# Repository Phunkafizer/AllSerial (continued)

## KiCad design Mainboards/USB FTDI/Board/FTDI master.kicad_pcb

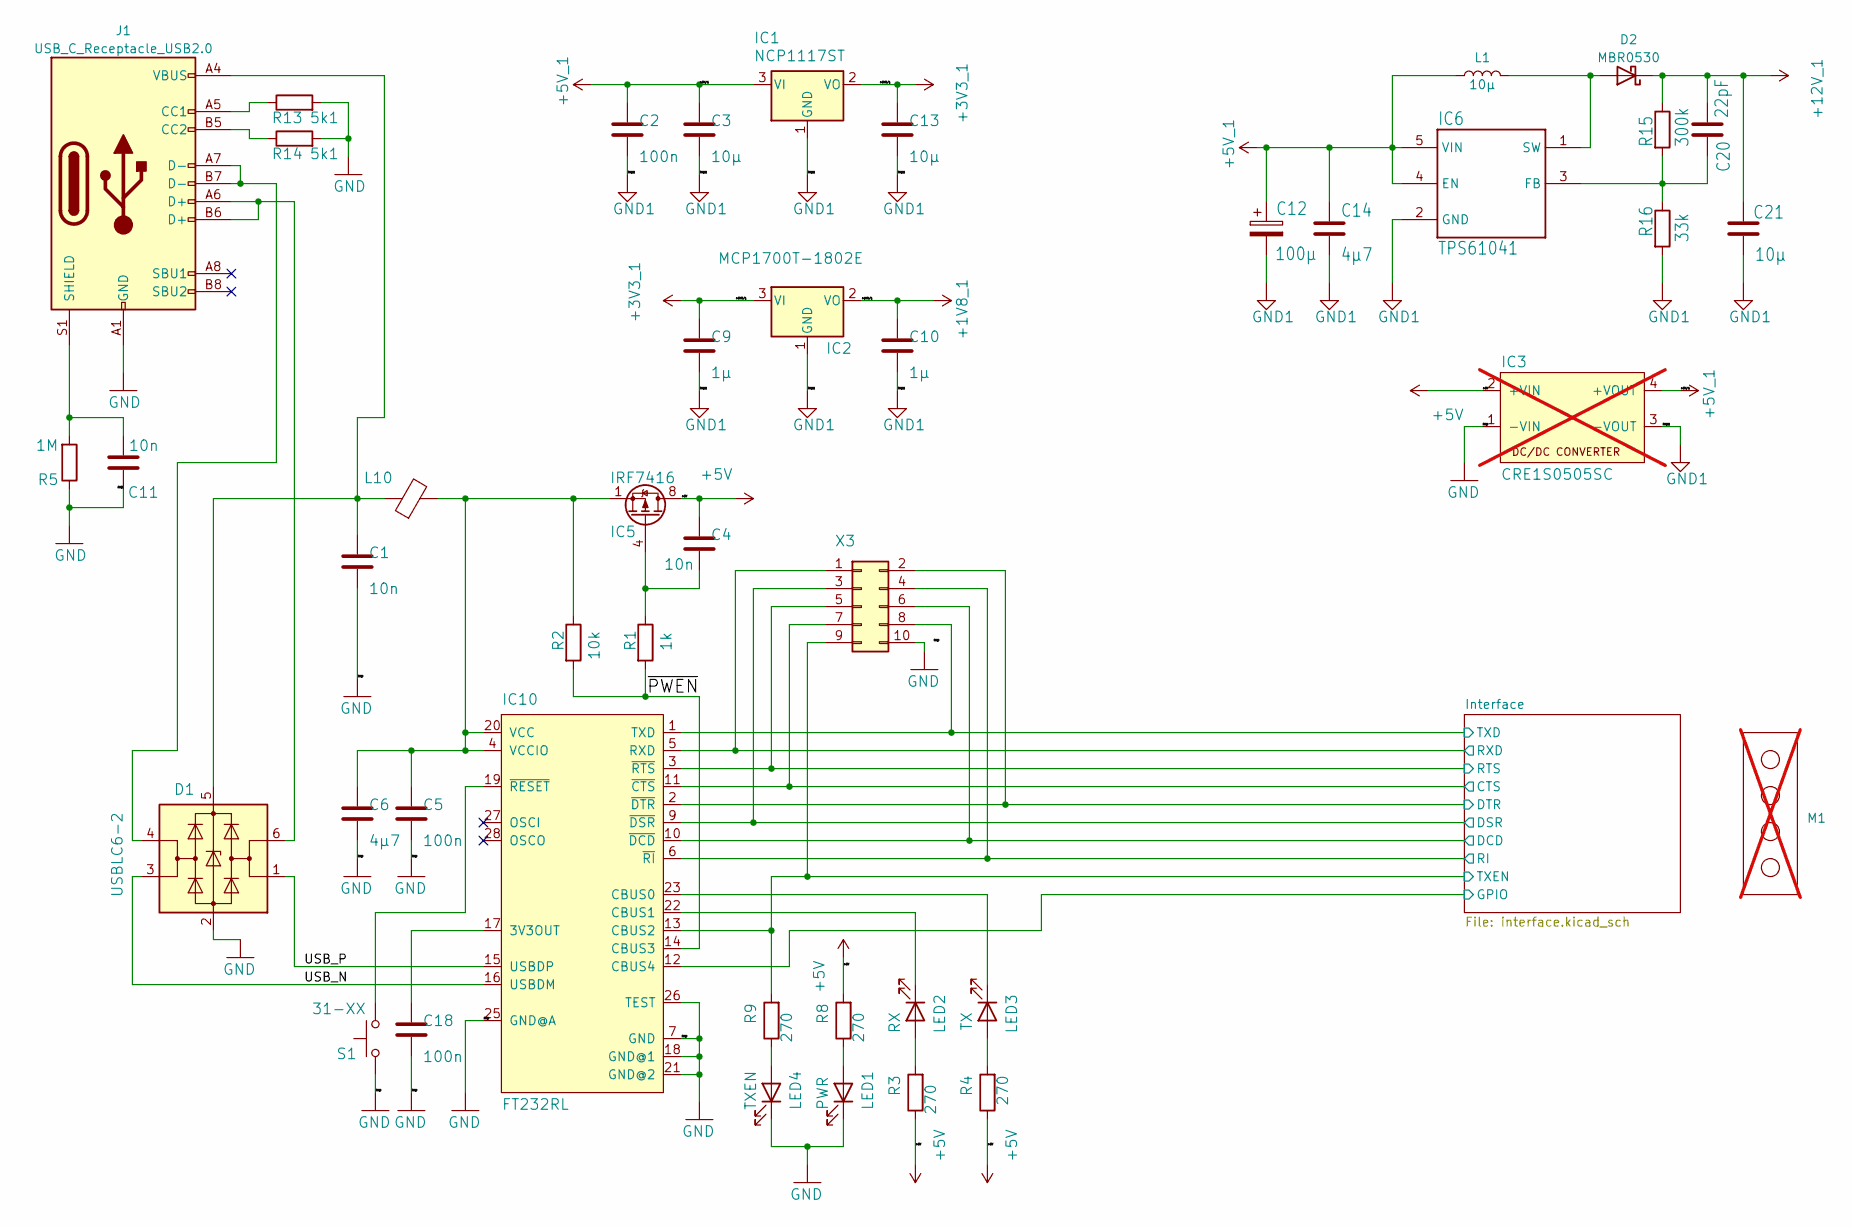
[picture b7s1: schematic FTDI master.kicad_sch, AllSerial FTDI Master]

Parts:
C1, C4, C11: 10n; C_0805_2012Metric; LCSC C1710
C2, C5, C18: 100n; C_0603_1608Metric; LCSC C14663
C3, C13: 10µ; C_0805_2012Metric; LCSC C90544
C6, C14: 4µ7; C_0805_2012Metric; LCSC C2918489
C9, C10: 1µ; C_0805_2012Metric; LCSC C111768
C12: 100µ; CP_Elec_5x5.9; LCSC C129417
C20: 22pF; C_0805_2012Metric; LCSC C105623
C21: 10µ; C_0805_2012Metric; LCSC C15850
D1: USBLC6-2; SOT-23-6; LCSC C5197386
D2: MBR0530; D_SOD-123; LCSC C475718
IC1: NCP1117ST; SOT-223-3_TabPin2; LCSC C26537
IC2: MCP1700T-1802E; SOT-23; LCSC C150796
IC3: CRE1S0505SC; MURATA-SC; not fitted
IC5: IRF7416; SOIC-8_3.9x4.9mm_P1.27mm; LCSC C5261058
IC6: TPS61041; SOT-23-5_HandSoldering; LCSC C9846
IC10: FT232RL; SSOP-28_5.3x10.2mm_P0.65mm; LCSC C8690
J1: USB_C_Receptacle_USB2.0; USB_C_Receptacle_G-Switch_GT-USB-7010ASV; LCSC C2927037
L1: 10µ; L_1210_3225Metric; LCSC C2041531
L10: L_0805_2012Metric; LCSC C76817
LED1: PWR; LED_0603_1608Metric; LCSC C2986058
LED2: RX; LED_0603_1608Metric; LCSC C2986030
LED3: TX; LED_0603_1608Metric; LCSC C2986060
LED4: TXEN; LED_0603_1608Metric; LCSC C2986063
M1: Mentor 1296.1004; not fitted
R1: 1k; R_0805_2012Metric; LCSC C17513
R2: 10k; R_0805_2012Metric; LCSC C17414
R3, R4, R8, R9: 270; R_0805_2012Metric; LCSC C93657
R5: 1M; R_0805_2012Metric; LCSC C3152182
R13, R14: 5k1; R_0805_2012Metric; LCSC C27834
R15: 300k; R_0805_2012Metric; LCSC C17616
R16: 33k; R_0805_2012Metric; LCSC C17633
S1: 31-XX; SW_SPST_Omron_B3F-315x_Angled
X3: IDC-Header_2x05_P2.54mm_Vertical; LCSC C429962

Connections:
+1V8_1: C10.1, IC2.2 (VO); also elsewhere on the board
+3V3_1: C9.1, C13.1, IC1.2 (VO), IC2.3 (VI); also elsewhere on the board
+5V: C4.1, IC3.2 (+VIN), IC5.5 (D), IC5.6 (D), IC5.7 (D), IC5.8 (D), R3.1, R4.1, R8.2; also elsewhere on the board
+5V_1: C2.1, C3.1, C12.1, C14.1, IC1.3 (VI), IC3.4 (+VOUT), IC6.4 (EN), IC6.5 (VIN), L1.1; also elsewhere on the board
+12V_1: C20.1, C21.1, D2.1 (K), R15.1; also elsewhere on the board
/Interface/CTS: IC10.11 (~CTS), X3.7; also elsewhere on the board
/Interface/DCD: IC10.10 (~DCD), X3.6; also elsewhere on the board
/Interface/DSR: IC10.9 (~DSR), X3.3; also elsewhere on the board
/Interface/DTR: IC10.2 (~DTR), X3.2; also elsewhere on the board
/Interface/GPIO: IC10.12 (CBUS4); also elsewhere on the board
/Interface/RI: IC10.6 (~RI), X3.4; also elsewhere on the board
/Interface/RTS: IC10.3 (~RTS), X3.5; also elsewhere on the board
/Interface/RXD: IC10.5 (RXD), X3.1; also elsewhere on the board
/Interface/TXD: IC10.1 (TXD), X3.8; also elsewhere on the board
/Interface/TXEN: IC10.13 (CBUS2), R9.2, X3.9; also elsewhere on the board
/USB_N: D1.3 (I/O2), IC10.16 (USBDM)
/USB_P: D1.1 (I/O1), IC10.15 (USBDP)
/~PWEN: IC10.14 (CBUS3), R1.2, R2.2
GND: C1.2, C5.2, C6.2, C11.2, C18.2, D1.2 (GND), IC3.1 (-VIN), IC10.7 (GND), IC10.18 (GND@1), IC10.21 (GND@2), IC10.25 (GND@A), IC10.26 (TEST), J1.A1 (GND), J1.A12 (GND), J1.B1 (GND), J1.B12 (GND), LED1.1 (K), LED4.1 (K), R5.1, R13.2, R14.2, S1.1, X3.10; also elsewhere on the board
GND1: C2.2, C3.2, C9.2, C10.2, C12.2, C13.2, C14.2, C21.2, IC1.1 (GND), IC2.1 (GND), IC3.3 (-VOUT), IC6.2 (GND), R16.2; also elsewhere on the board
unnamed: D1.6 (I/O1), J1.A6 (D+), J1.B6 (D+)
unnamed: D1.4 (I/O2), J1.A7 (D-), J1.B7 (D-)
unnamed: C1.1, D1.5 (VBUS), J1.A4 (VBUS), J1.A9 (VBUS), J1.B4 (VBUS), J1.B9 (VBUS), L10.1
unnamed: D2.2 (A), IC6.1 (SW), L1.2
unnamed: C4.2, IC5.4 (G), R1.1
unnamed: C20.2, IC6.3 (FB), R15.2, R16.1
unnamed: C18.1, IC10.17 (3V3OUT)
unnamed: IC10.23 (CBUS0), LED3.1 (K)
unnamed: IC10.22 (CBUS1), LED2.1 (K)
unnamed: C5.1, C6.1, IC5.1 (S), IC5.2 (S), IC5.3 (S), IC10.4 (VCCIO), IC10.20 (VCC), L10.2, R2.1
unnamed: IC10.19 (~RESET), S1.2
unnamed: J1.A5 (CC1), R13.1
unnamed: J1.B5 (CC2), R14.1
unnamed: C11.1, J1.S1 (SHIELD), R5.2
unnamed: LED1.2 (A), R8.1
unnamed: LED2.2 (A), R3.2
unnamed: LED3.2 (A), R4.2
unnamed: LED4.2 (A), R9.1

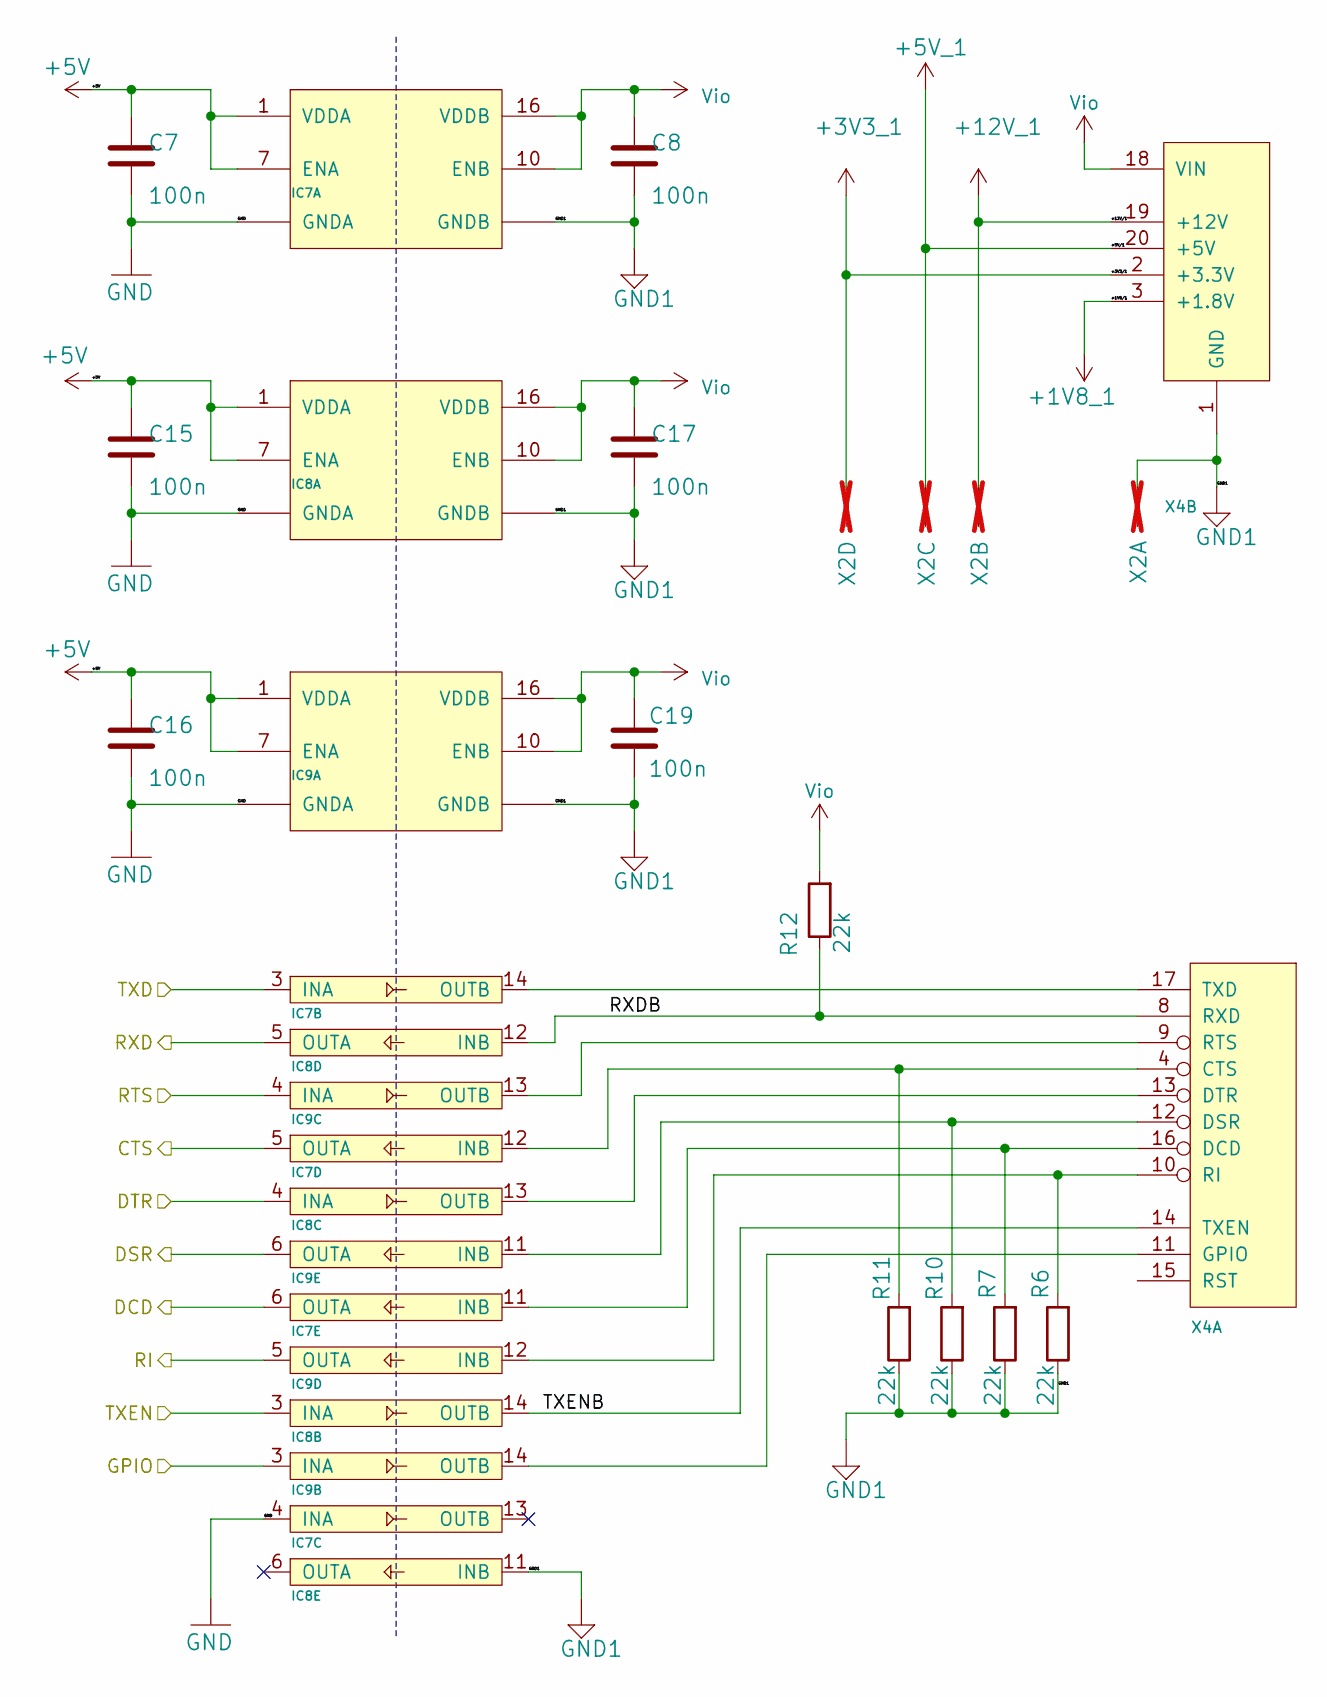
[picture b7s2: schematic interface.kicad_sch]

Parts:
C7, C8, C15, C16, C17, C19: 100n; C_0603_1608Metric; LCSC C14663
IC7, IC8, IC9: ADuM142E0BRQZ-RL7; QSOP-16_3.9x4.9mm_P0.635mm; LCSC C660448
R6, R7, R10, R11, R12: 22k; R_0805_2012Metric
X2: AKL18X-04W; Metz_PT11304HBBN_182; not fitted
X4: ALLSERIALMASTERM; MasterBoard; LCSC C124406

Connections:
+1V8_1: X4.3 (+1.8V); also elsewhere on the board
+3V3_1: X2.P$4 (S), X4.2 (+3.3V); also elsewhere on the board
+5V: C7.1, C15.1, C16.1, IC7.1 (VDDA), IC7.7 (ENA), IC8.1 (VDDA), IC8.7 (ENA), IC9.1 (VDDA), IC9.7 (ENA); also elsewhere on the board
+5V_1: X2.P$3 (S), X4.20 (+5V); also elsewhere on the board
+12V_1: X2.P$2 (S), X4.19 (+12V); also elsewhere on the board
/Interface/CTS: IC7.5 (OUTA); also elsewhere on the board
/Interface/DCD: IC7.6 (OUTA); also elsewhere on the board
/Interface/DSR: IC9.6 (OUTA); also elsewhere on the board
/Interface/DTR: IC8.4 (INA); also elsewhere on the board
/Interface/GPIO: IC9.3 (INA); also elsewhere on the board
/Interface/RI: IC9.5 (OUTA); also elsewhere on the board
/Interface/RTS: IC9.4 (INA); also elsewhere on the board
/Interface/RXD: IC8.5 (OUTA); also elsewhere on the board
/Interface/RXDB: IC8.12 (INB), R12.1, X4.8 (RXD)
/Interface/TXD: IC7.3 (INA); also elsewhere on the board
/Interface/TXEN: IC8.3 (INA); also elsewhere on the board
/Interface/TXENB: IC8.14 (OUTB), X4.14 (TXEN)
GND: C7.2, C15.2, C16.2, IC7.2 (GNDA), IC7.4 (INA), IC7.8 (GNDA), IC8.2 (GNDA), IC8.8 (GNDA), IC9.2 (GNDA), IC9.8 (GNDA); also elsewhere on the board
GND1: C8.2, C17.2, C19.2, IC7.9 (GNDB), IC7.15 (GNDB), IC8.9 (GNDB), IC8.11 (INB), IC8.15 (GNDB), IC9.9 (GNDB), IC9.15 (GNDB), R6.1, R7.1, R10.1, R11.1, X2.P$1 (S), X4.1 (GND); also elsewhere on the board
unnamed: IC7.14 (OUTB), X4.17 (TXD)
unnamed: IC7.12 (INB), R11.2, X4.4 (CTS)
unnamed: IC7.11 (INB), R7.2, X4.16 (DCD)
unnamed: IC8.13 (OUTB), X4.13 (DTR)
unnamed: IC9.14 (OUTB), X4.11 (GPIO)
unnamed: IC9.13 (OUTB), X4.9 (RTS)
unnamed: IC9.12 (INB), R6.2, X4.10 (RI)
unnamed: IC9.11 (INB), R10.2, X4.12 (DSR)
Vio: C8.1, C17.1, C19.1, IC7.10 (ENB), IC7.16 (VDDB), IC8.10 (ENB), IC8.16 (VDDB), IC9.10 (ENB), IC9.16 (VDDB), R12.2, X4.18 (VIN)

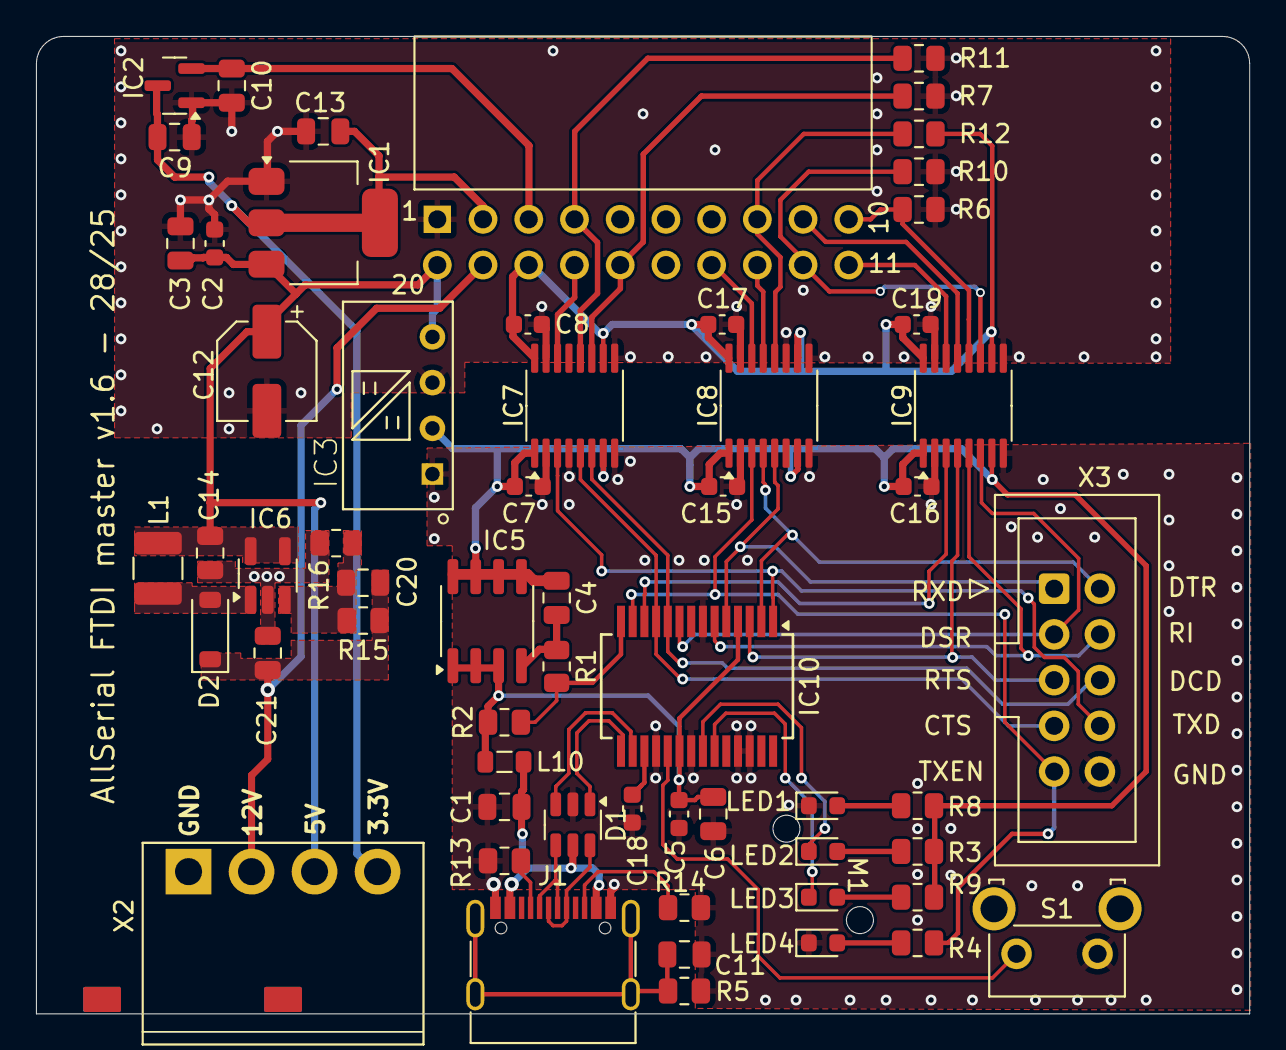
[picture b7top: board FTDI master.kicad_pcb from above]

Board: 2 copper layers, 67.4 x 54.3 mm, 60 parts (0 on the bottom side), 49 nets.

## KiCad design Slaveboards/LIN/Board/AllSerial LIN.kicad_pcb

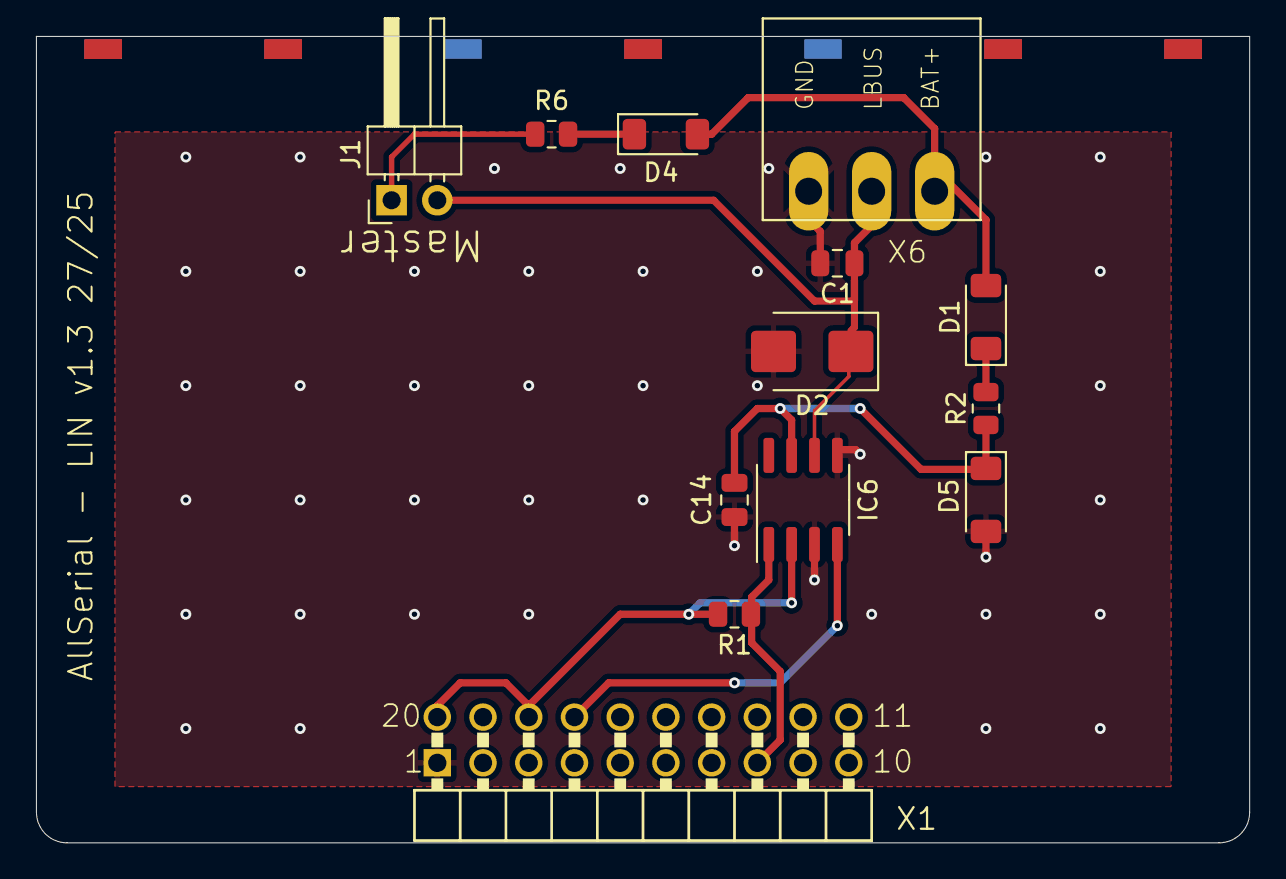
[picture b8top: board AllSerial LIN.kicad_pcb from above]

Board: 2 copper layers, 67.4 x 44.8 mm, 13 parts (0 on the bottom side), 10 nets.

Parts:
C1: 220p; C_0805_2012Metric
C14: 1µ; C_0805_2012Metric
D1, D4: 1N4148; D_MiniMELF
D2: SM6T27A; D_SMB
D5: 43V; D_MiniMELF
IC6: MCP2003; SOIC-8_3.9x4.9mm_P1.27mm
J1: MA02-1W; PinHeader_1x02_P2.54mm_Horizontal
R1: 4k7; R_0805_2012Metric
R2: 47; R_0805_2012Metric
R6: 1k; R_0805_2012Metric
X1: ALLSERIALSLAVE; SlaveBoard
X6: AKL18X-03W; Metz_PT11303HBBN_182

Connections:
+5V: IC6.2 (CS), R1.2, X1.18 (VIN), X1.20 (+5V)
GND: C1.2, C14.2, D2.2 (A), D5.2 (A), IC6.3 (~WAKE), IC6.5 (VSS), X1.1 (GND), X6.3
unnamed: D1.1 (K), R2.2
unnamed: C1.1, D2.1 (K), IC6.6 (LBUS), J1.2 (B), X6.2
unnamed: D4.1 (K), R6.1
unnamed: C14.1, D5.1 (K), IC6.7 (VBB), R2.1
unnamed: IC6.1 (RXD), R1.1, X1.8 (RXD)
unnamed: IC6.4 (TXD), X1.17 (TXD)
unnamed: J1.1 (A), R6.2
VCC: D1.2 (A), D4.2 (A), X6.1

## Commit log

2018-07-07 add mainboard front panel image
2018-07-07 adding schematic & images
2018-07-07 update images
2018-07-07 imagetest
2018-07-07 remove imagetests
2018-07-07 Corrected RST pin
2018-07-07 RS232 routing
2018-07-07 board seperation
2018-07-07 update lib
2018-07-08 Improve lib
    Route RS232 board
    Route TTL board
2018-07-10 Add USB pins
2018-07-10 finish LIN schematic
2018-07-12 update lib
    restructured
2018-07-12 correct paths
2018-07-12 added mBus master
2018-07-12 updated readme & mainboard
2018-07-12 insert diode for supply
2018-07-17 Add 2mm front line
2018-07-17 finish FTDI PCB
2018-07-17 finish RS485 PCB
2018-07-17 fix connector for LA
2018-07-18 Add ESD protection
2018-07-18 Add BOM
2018-07-18 add and correct BOMs
2018-07-20 new BOMs,
    finish TTY board
2018-07-20 add schematics
2018-07-25 Clean up
2018-07-25 renaming, add front
2018-07-25 add front
2018-07-25 change diodes
2018-07-31 add author
2018-09-01 change to libv2
2018-09-01 update graphics
2018-09-21 new lib, change pinout!
2018-09-26 final design & order
2018-09-26 use new lib
2018-09-26 fix measure layer
2018-10-01 Update BOM & pics
2018-10-01 Add order codes
2018-10-01 update BOM
2018-10-03 fix BOM for MAX211
2018-10-07 add eagle front boards
2018-10-07 cleanup
2018-10-07 fix GND connection
2018-10-07 update boms
2018-10-09 renaming
2018-10-09 update bills of material
2018-10-09 Add front, update png, clean up
2018-10-09 update png & cleanup
2018-10-09 fix link
2018-10-09 fix dir
2018-10-09 fix image link
2018-10-12 BOM updates
2018-10-15 correct connector labels
2018-10-15 smaller images
2018-10-15 image resize
2018-10-22 more readme
2018-10-22 more readme & pics
2018-10-22 rename pic
2018-10-22 correct link
2018-10-23 Update PDF
2018-10-23 add pdf docs
    add gerber data
    cleanup
    renaming
2018-10-23 layout
2018-10-23 Create LICENSE
2018-10-30 added 10 arduino module
2018-10-30 add 1wire files
2018-10-30 add front boards
2018-11-03 adding 1wire and eBus boards
2018-11-03 add ESP & arduino board
2018-11-03 Update Link
2018-11-19 pro mini layout corrected
2018-11-19 Revert "pro mini layout corrected"
    This reverts commit e6acf7b114fc184efa746b3a51c54623d1353390.
2018-11-19 Use lib elements
2018-11-19 Cleanup, front with lib elements
2018-11-19 Revert "Cleanup, front with lib elements"
    This reverts commit d2aae2c670d4479654c143ea750e88e2046a00ae.
2018-11-19 Cleanup, front lib elements
2018-11-19 cleanup & update docu
2024-07-19 Truncated hist
2024-07-19 Added new boards
2024-07-19 add WiFi Master Front
    add symbol lib for fronts
2024-07-19 Update AllSerial libraries
    update projects
    add slave project template
2024-07-19 Migrate to new KiCad Version
    Add SMA connector front
2024-07-19 Update TTY CL slave board
    Add ESP32 S3 WiFi MasterBoard
    Update libs
2024-07-19 add images
    update readme
2024-07-23 improve board/front links
    clean up
2025-07-08 Migrate to KiCad 9
    Add eBus board
    Add various libraries
2025-07-09 improve AllSerial library
    add assets for README
    update README
    cleanup
2025-07-09 add frontpanel STEP files
2025-07-16 Improve libraries
2025-07-20 Remove pads from cutouts
2025-08-07 FTDI master: Change footprint of isolators
    minor improvments
2025-08-21 Add python testskript
    Add mainboard tester
    Add libraries
2025-08-21 add wiring schemes
